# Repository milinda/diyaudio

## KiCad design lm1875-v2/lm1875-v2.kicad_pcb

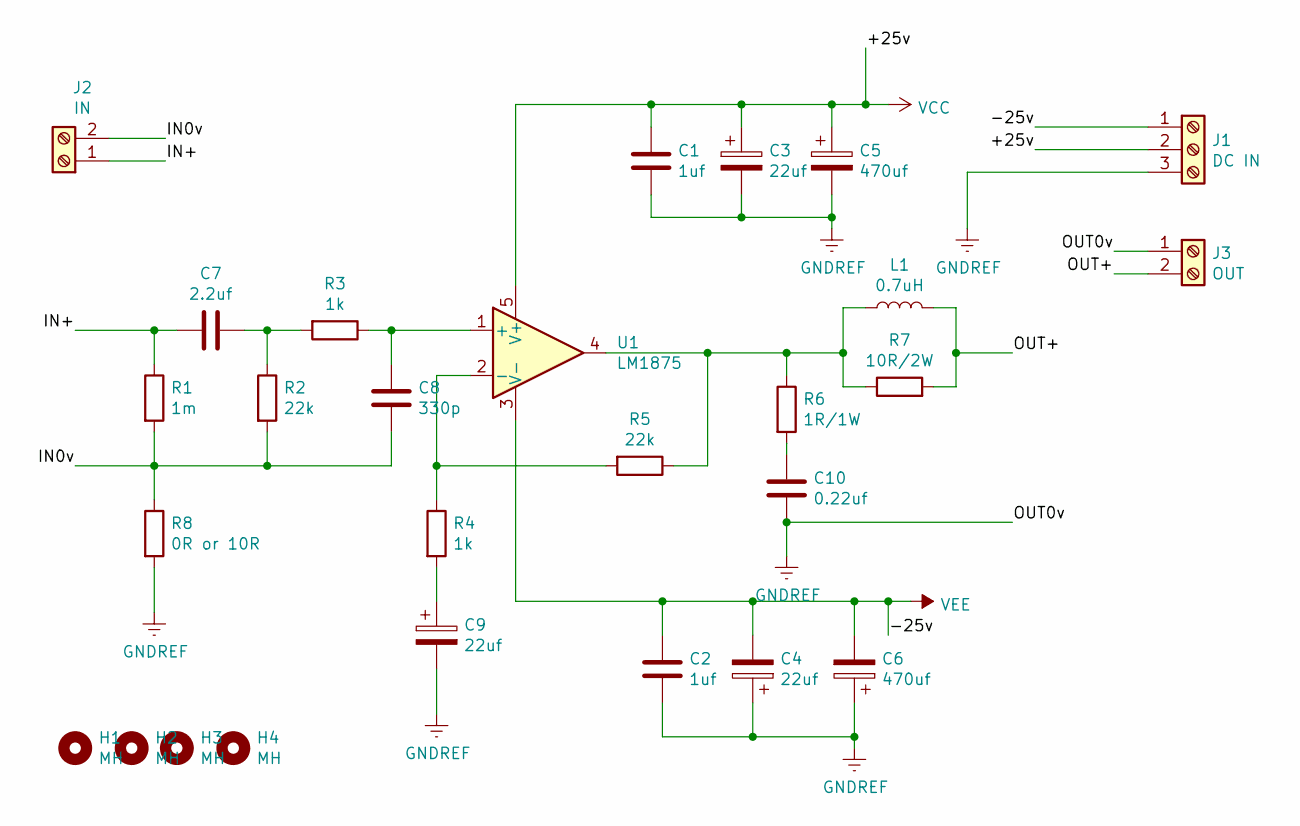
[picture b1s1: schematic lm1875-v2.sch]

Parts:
C1, C2: 1uf; C_Disc_D6.0mm_W2.5mm_P5.00mm; Mouser 810-FK24X7R1H105K
C3, C4: 22uf; CP_Radial_D6.3mm_P2.50mm; Mouser 667-35SEPF22M
C5, C6: 470uf; CP_Radial_D10.0mm_P5.00mm; Mouser 647-UVK1H471MPD1TD
C7: 2.2uf; C_Rect_L10.3mm_W5.7mm_P7.50mm_MKS4; Mouser 505-MKS42.2/50/5
C8: 330p; C_Rect_L7.2mm_W4.5mm_P5.00mm_FKS2_FKP2_MKS2_MKP2; Mouser 505-FKP2C003301DJI00
C9: 22uf; CP_Radial_D5.0mm_P2.00mm; Mouser 647-UPW1H221MPD1TD
C10: 0.22uf; C_Rect_L10.0mm_W3.0mm_P7.50mm_MKS4; Mouser 505-MKS4C032202BKSSD
H1, H2, H3, H4: MH; MountingHole_2.2mm_M2
J1: DC IN; TerminalBlock_Phoenix_MKDS-1,5-3-5.08_1x03_P5.08mm_Horizont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; Mouser 651-1985975
J2: IN; TerminalBlock_Phoenix_MKDS-1,5-2-5.08_1x02_P5.08mm_Horizont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
J3: OUT; TerminalBlock_Phoenix_MKDS-1,5-2-5.08_1x02_P5.08mm_Horizont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
L1: 0.7uH; R_Axial_DIN0516_L15.5mm_D5.0mm_P20.32mm_Horizontal; Mouser 434-HCCC-R70M-02
R1: 1m; R_Axial_DIN0207_L6.3mm_D2.5mm_P10.16mm_Horizontal; Mouser 660-MF1/4DCT52R1004F
R2, R5: 22k; R_Axial_DIN0207_L6.3mm_D2.5mm_P10.16mm_Horizontal; Mouser 660-MF1/4DCT52R2202F
R3, R4: 1k; R_Axial_DIN0207_L6.3mm_D2.5mm_P10.16mm_Horizontal; Mouser 660-MF1/4DCT52A1001F
R6: 1R/1W; R_Axial_DIN0414_L11.9mm_D4.5mm_P15.24mm_Horizontal; Mouser 594-MBE04140C1008FC1
R7: 10R/2W; R_Axial_DIN0516_L15.5mm_D5.0mm_P20.32mm_Horizontal; Mouser 603-MFR200FRF52-10R
R8: 0R or 10R; R_Axial_DIN0207_L6.3mm_D2.5mm_P10.16mm_Horizontal; Mouser 660-MF1/4DCT52R10R0F
U1: LM1875; TO-220-5_P3.4x3.7mm_StaggerOdd_Lead3.8mm_Vertical

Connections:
/IN0v: C8.2, J2.2, R1.2, R2.2, R8.1
/IN+: C7.2, J2.1, R1.1
/OUT+: J3.2, L1.2, R7.2
GNDREF: C1.2, C2.2, C3.2, C4.1, C5.2, C6.1, C9.2, C10.2, J1.3, J3.1, R8.2
unnamed: C7.1, R2.1, R3.2
unnamed: C8.1, R3.1, U1.1 (+)
unnamed: C9.1, R4.2
unnamed: C10.1, R6.2
unnamed: L1.1, R5.1, R6.1, R7.1, U1.4
unnamed: R4.1, R5.2, U1.2 (-)
VCC: C1.1, C3.1, C5.1, J1.2, U1.5 (V+)
VEE: C2.1, C4.2, C6.2, J1.1, U1.3 (V-)

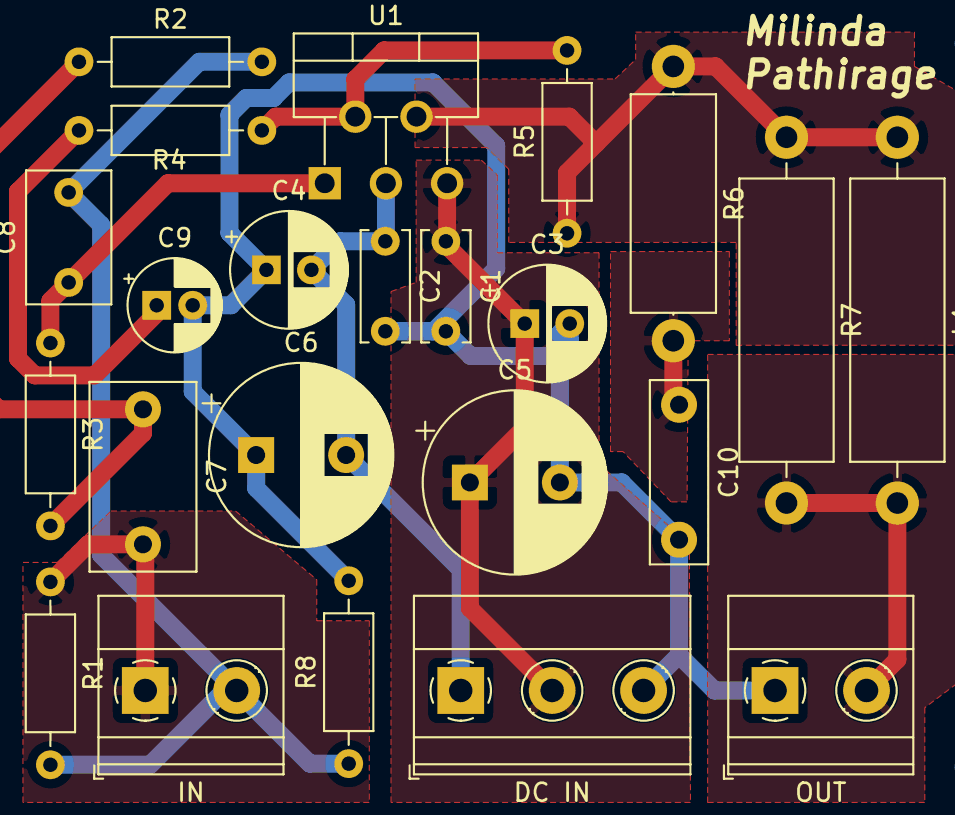
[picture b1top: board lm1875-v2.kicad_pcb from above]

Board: 2 copper layers, 27 parts (0 on the bottom side), 12 nets.

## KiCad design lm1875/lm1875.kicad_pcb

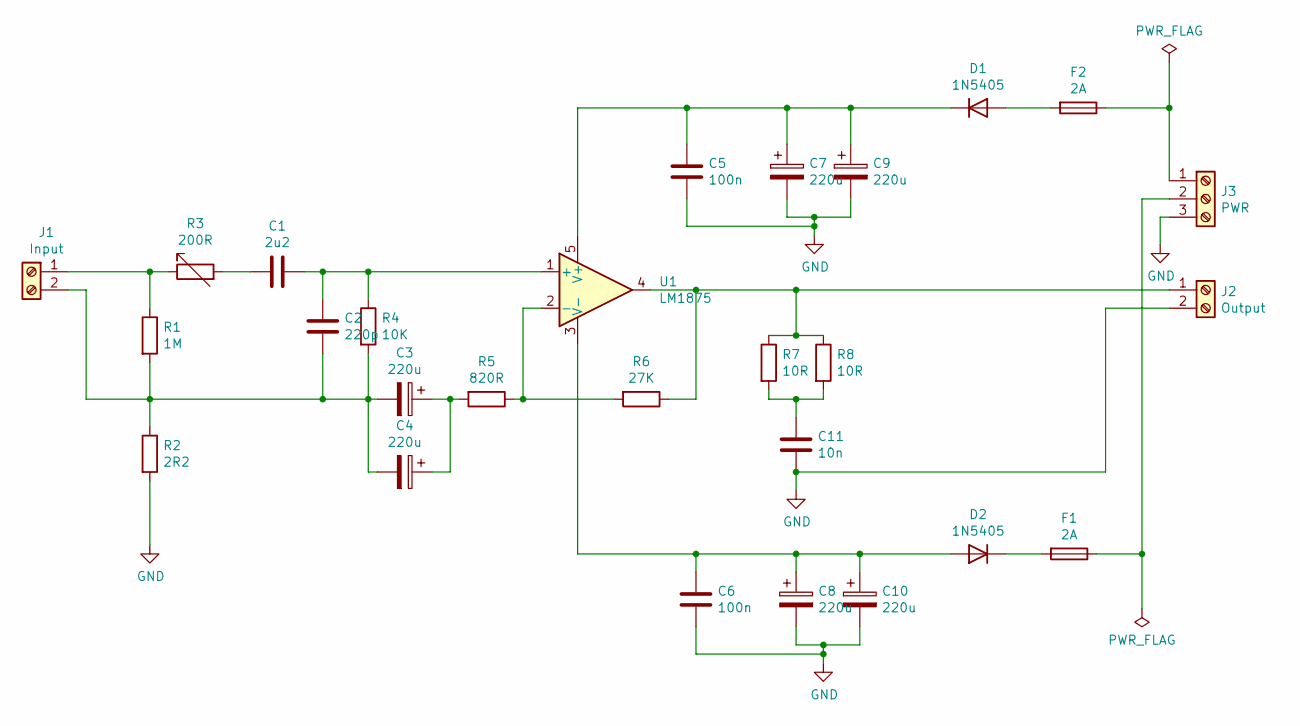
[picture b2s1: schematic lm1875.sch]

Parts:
C1: 2u2; C_Rect_L7.2mm_W7.2mm_P5.00mm_FKS2_FKP2_MKS2_MKP2; Mouser 505-MKS22.2/63/5
C2: 220p; C_Rect_L7.2mm_W4.5mm_P5.00mm_FKS2_FKP2_MKS2_MKP2; Mouser 505-FKP2C002201D00KI
C3, C7, C8, C9, C10: 220u; CP_Radial_D10.0mm_P5.00mm; Mouser 647-UKA1H221MPD1TD
C4: 220u; CP_Radial_D10.0mm_P5.00mm
C5, C6: 100n; C_Rect_L7.2mm_W2.5mm_P5.00mm_FKS2_FKP2_MKS2_MKP2; Mouser 505-MKS2.1/63/5T
C11: 10n; C_Rect_L7.2mm_W2.5mm_P5.00mm_FKS2_FKP2_MKS2_MKP2; Mouser 505-MKS2.01/63/5T
D1, D2: 1N5405; D_DO-201AD_P15.24mm_Horizontal
F1, F2: 2A; Fuseholder_Cylinder-5x20mm_Schurter_0031_8201_Horizontal_Op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
J1: Input; TerminalBlock_Phoenix_MKDS-1,5-2_1x02_P5.00mm_Horizontal; Mouser 651-1711026
J2: Output; TerminalBlock_Phoenix_MKDS-1,5-2_1x02_P5.00mm_Horizontal; Mouser 651-1711026
J3: PWR; TerminalBlock_Phoenix_MKDS-1,5-3_1x03_P5.00mm_Horizontal; Mouser 651-1714023
R1: 1M; R_Axial_DIN0207_L6.3mm_D2.5mm_P10.16mm_Horizontal; Mouser 660-MF1/4DC1004F
R2: 2R2; R_Axial_DIN0207_L6.3mm_D2.5mm_P10.16mm_Horizontal; Mouser 660-MF1/4DCT52R2R20F
R3: 200R; Potentiometer_Bourns_3296W_Vertical; Mouser 652-3296W-1-201RLF
R4: 10K; R_Axial_DIN0207_L6.3mm_D2.5mm_P10.16mm_Horizontal; Mouser 660-MF1/4DCVTR1002F
R5: 820R; R_Axial_DIN0207_L6.3mm_D2.5mm_P10.16mm_Horizontal
R6: 27K; R_Axial_DIN0207_L6.3mm_D2.5mm_P10.16mm_Horizontal
R7, R8: 10R; R_Axial_DIN0207_L6.3mm_D2.5mm_P10.16mm_Horizontal
U1: LM1875; TO-220-5_P3.4x3.7mm_StaggerOdd_Lead3.8mm_Vertical

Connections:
GND: C5.2, C6.2, C7.2, C8.2, C9.2, C10.2, C11.2, J2.2, J3.3, R2.2
unnamed: C1.1, C2.1, R4.1, U1.1 (+)
unnamed: C1.2, R3.2
unnamed: C2.2, C3.2, C4.2, J1.2, R1.2, R2.1, R4.2
unnamed: C3.1, C4.1, R5.2
unnamed: C5.1, C7.1, C9.1, D1.1 (K), U1.5 (V+)
unnamed: C6.1, C8.1, C10.1, D2.2 (A), U1.3 (V-)
unnamed: C11.1, R7.2, R8.2
unnamed: D1.2 (A), F2.2
unnamed: D2.1 (K), F1.2
unnamed: F1.1, J3.2
unnamed: F2.1, J3.1
unnamed: J1.1, R1.1, R3.1
unnamed: J2.1, R6.1, R7.1, R8.1, U1.4
unnamed: R5.1, R6.2, U1.2 (-)

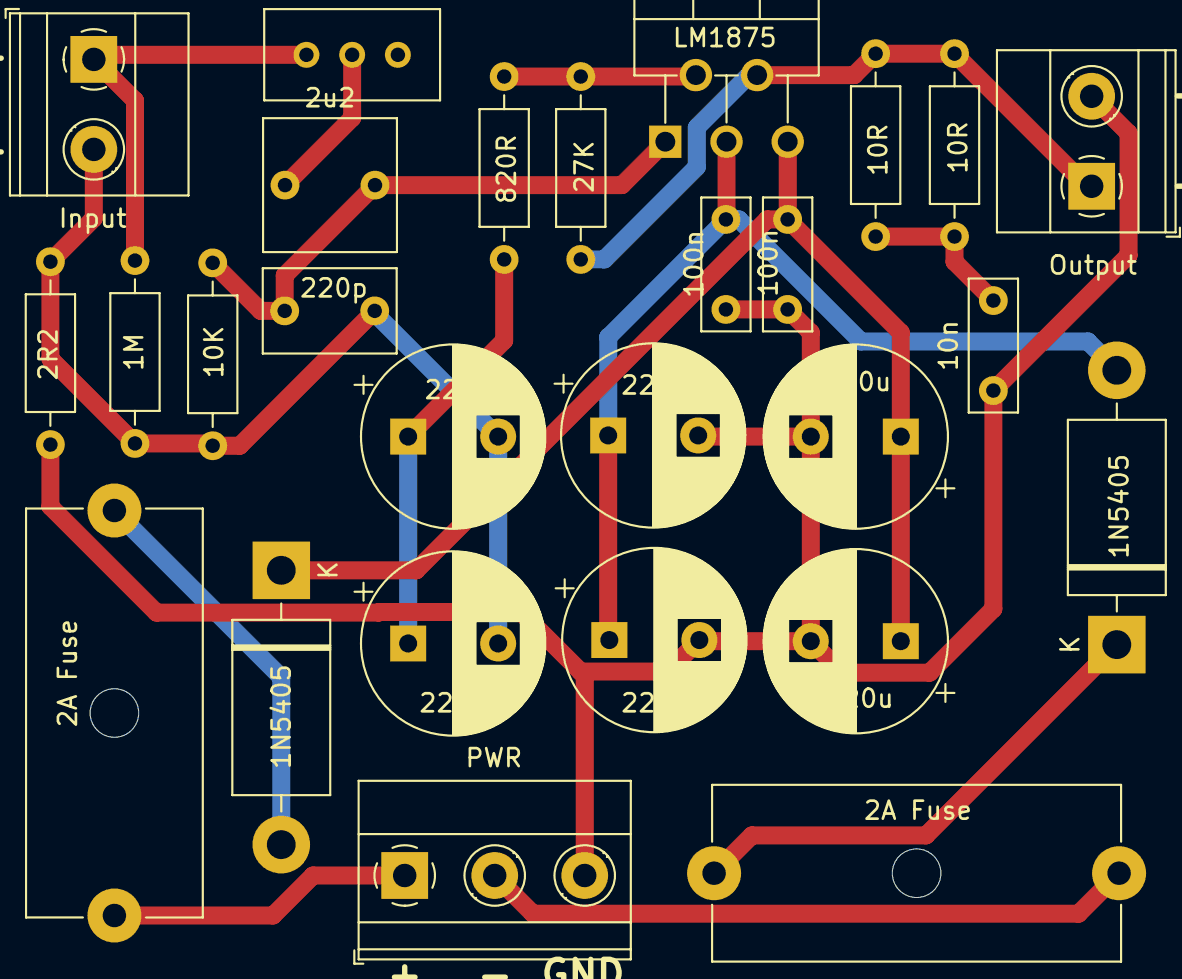
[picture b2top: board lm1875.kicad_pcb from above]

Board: 2 copper layers, 27 parts (0 on the bottom side), 15 nets.

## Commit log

2021-05-17 Initial LM1875 schematic and pcb
